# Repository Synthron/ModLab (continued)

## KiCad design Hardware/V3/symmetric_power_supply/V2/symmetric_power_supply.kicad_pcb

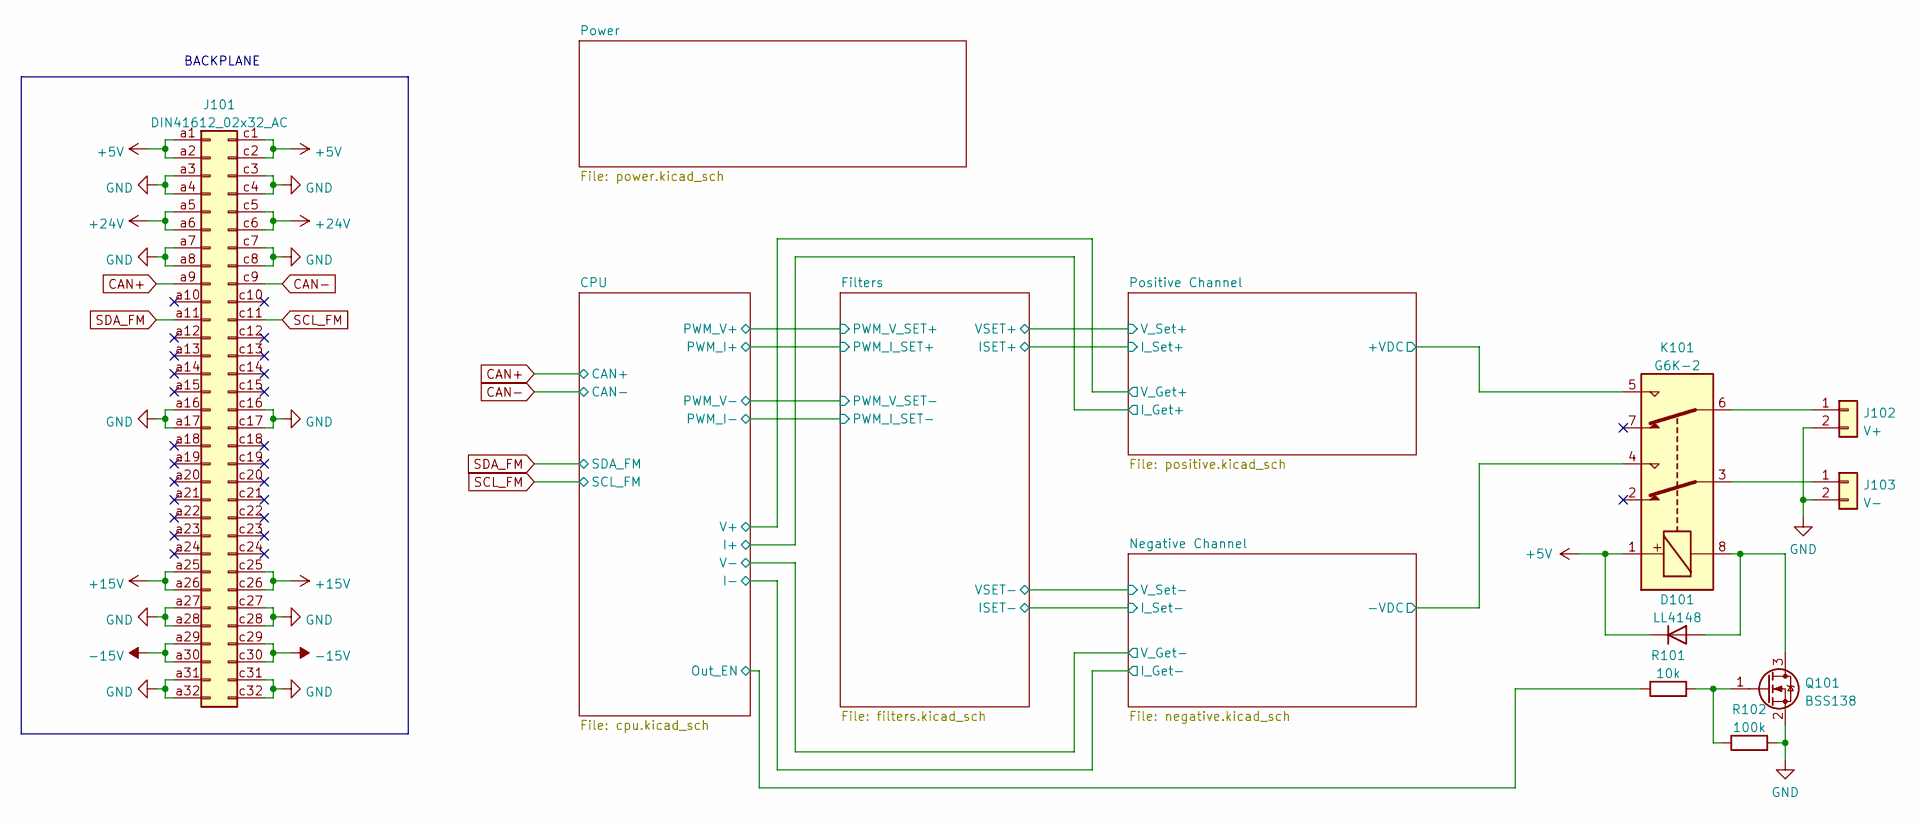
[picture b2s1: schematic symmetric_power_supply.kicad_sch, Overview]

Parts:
D101: LL4148; D_MiniMELF
J101: DIN41612_02x32_AC; VG64_Euro
J102: V+; PinHeader_1x02_P2.54mm_Vertical
J103: V-; PinHeader_1x02_P2.54mm_Vertical
K101: G6K-2; Relay_DPDT_Omron_G6K-2F
Q101: BSS138; SOT-23
R101: 10k; R_0805_2012Metric
R102: 100k; R_0805_2012Metric

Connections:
+5V: D101.1 (K), J101.a1, J101.a2, J101.c1, J101.c2, K101.1; also elsewhere on the board
+15V: J101.a25, J101.a26, J101.c25, J101.c26; also elsewhere on the board
+24V: J101.a5, J101.a6, J101.c5, J101.c6; also elsewhere on the board
+VDC: K101.5; also elsewhere on the board
-15V: J101.a29, J101.a30, J101.c29, J101.c30; also elsewhere on the board
-VDC: K101.4; also elsewhere on the board
/CPU/Out_EN: R101.1; also elsewhere on the board
CAN+: J101.a9; also elsewhere on the board
CAN-: J101.c9; also elsewhere on the board
GND: J101.a3, J101.a4, J101.a7, J101.a8, J101.a16, J101.a17, J101.a27, J101.a28, J101.a31, J101.a32, J101.c3, J101.c4, J101.c7, J101.c8, J101.c16, J101.c17, J101.c27, J101.c28, J101.c31, J101.c32, J102.2, J103.2, Q101.2 (S), R102.2; also elsewhere on the board
unnamed: D101.2 (A), K101.8, Q101.3 (D)
unnamed: J102.1, K101.6
unnamed: J103.1, K101.3
unnamed: Q101.1 (G), R101.2, R102.1
SCL_FM: J101.c11; also elsewhere on the board
SDA_FM: J101.a11; also elsewhere on the board

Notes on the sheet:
BACKPLANE

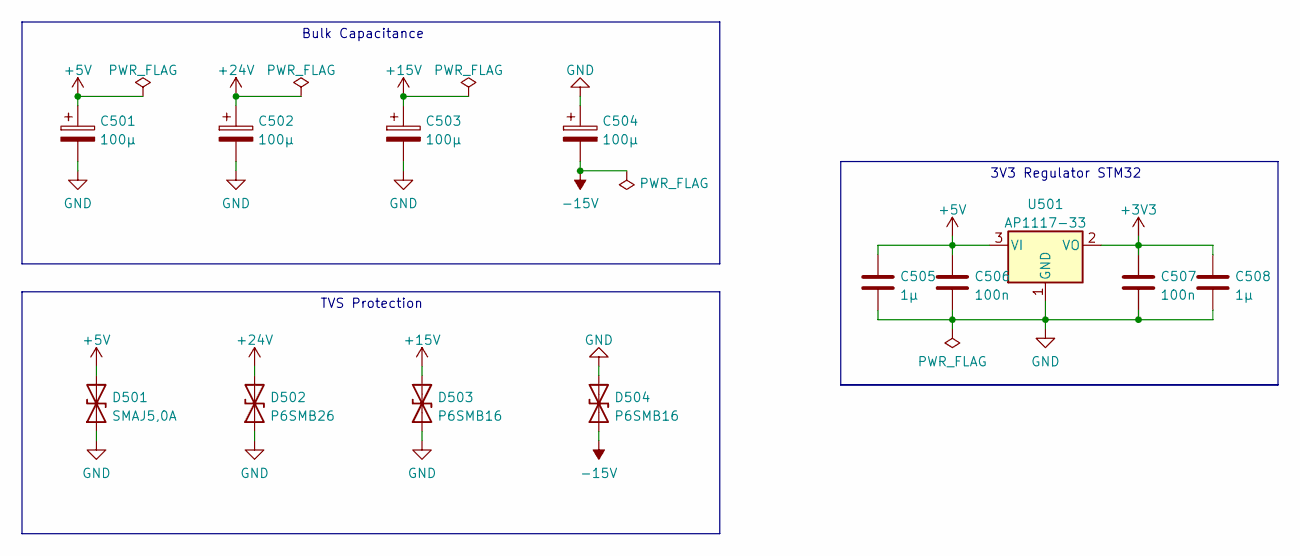
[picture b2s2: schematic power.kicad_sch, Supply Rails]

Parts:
C501, C502, C503, C504: 100µ; CP_Radial_D8.0mm_P5.00mm
C505, C508: 1µ; C_0805_2012Metric
C506, C507: 100n; C_0805_2012Metric
D501: SMAJ5,0A; D_SMA
D502: P6SMB26; D_SMA
D503, D504: P6SMB16; D_SMA
U501: AP1117-33; SOT-223-3_TabPin2

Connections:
+3V3: C507.1, C508.1, U501.2 (VO); also elsewhere on the board
+5V: C501.1, C505.1, C506.1, D501.2 (A2), U501.3 (VI); also elsewhere on the board
+15V: C503.1, D503.2 (A2); also elsewhere on the board
+24V: C502.1, D502.2 (A2); also elsewhere on the board
-15V: C504.2, D504.1 (A1); also elsewhere on the board
GND: C501.2, C502.2, C503.2, C504.1, C505.2, C506.2, C507.2, C508.2, D501.1 (A1), D502.1 (A1), D503.1 (A1), D504.2 (A2), U501.1 (GND); also elsewhere on the board

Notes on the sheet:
Bulk Capacitance
TVS Protection
3V3 Regulator STM32

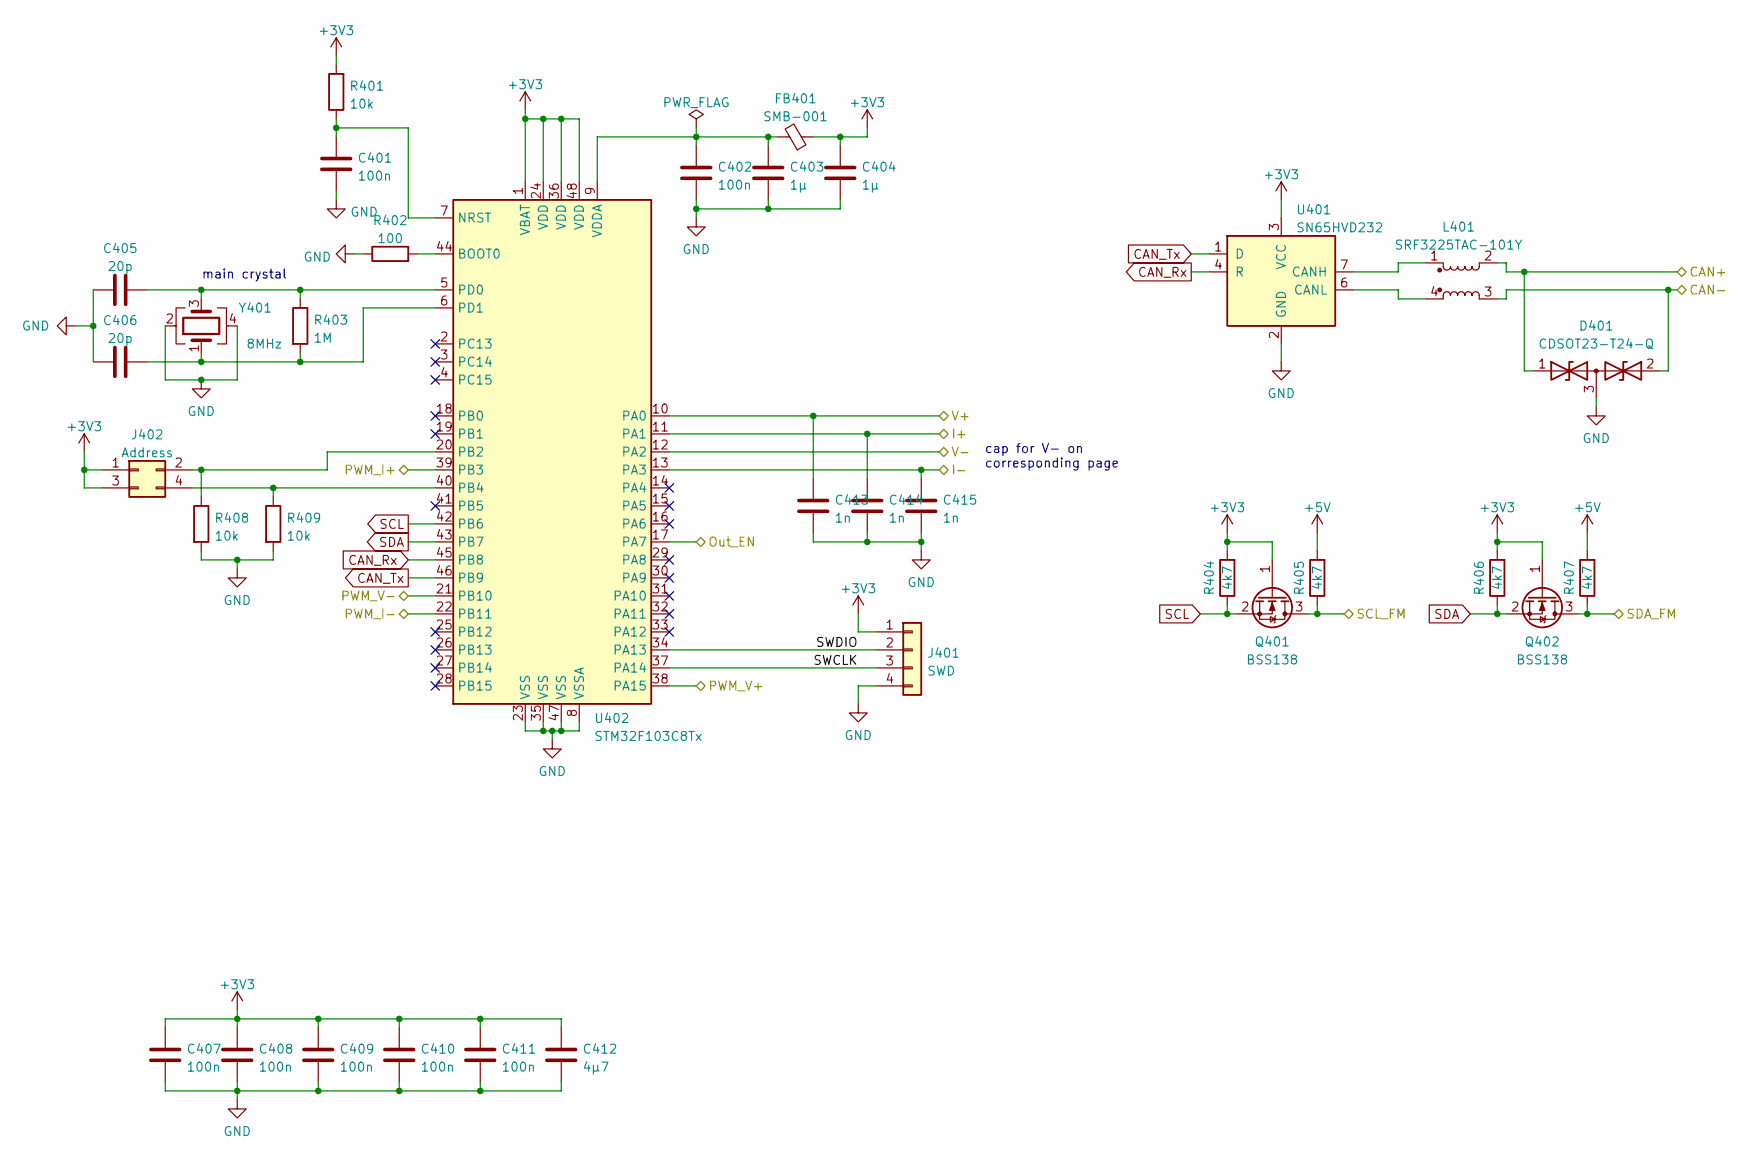
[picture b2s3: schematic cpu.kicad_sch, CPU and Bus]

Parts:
C401, C402, C407, C408, C409, C410, C411: 100n; C_0805_2012Metric
C403, C404: 1µ; C_0805_2012Metric
C405, C406: 20p; C_0805_2012Metric
C412: 4µ7; C_0805_2012Metric
C413, C414, C415: 1n; C_0805_2012Metric
D401: CDSOT23-T24-Q; SOT-23
FB401: SMB-001
J401: SWD; JST_XH_B4B-XH-A_1x04_P2.50mm_Vertical
J402: Address; PinHeader_2x02_P2.54mm_Vertical
L401: SRF3225TAC-101Y; SRF3225TAC
Q401, Q402: BSS138; SOT-23
R401, R408, R409: 10k; R_0805_2012Metric
R402: 100; R_0805_2012Metric
R403: 1M; R_0805_2012Metric
R404, R405, R406, R407: 4k7; R_0805_2012Metric
U401: SN65HVD232; SOIC-8_3.9x4.9mm_P1.27mm
U402: STM32F103C8Tx; LQFP-48_7x7mm_P0.5mm
Y401: 8MHz; Crystal_SMD_5032-4Pin_5.0x3.2mm

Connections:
+3V3: C404.1, C407.1, C408.1, C409.1, C410.1, C411.1, C412.1, FB401.1, J401.1, J402.1, J402.3, Q401.1 (G), Q402.1 (G), R401.2, R404.2, R406.2, U401.3 (VCC), U402.1 (VBAT), U402.24 (VDD), U402.36 (VDD), U402.48 (VDD); also elsewhere on the board
+5V: R405.2, R407.2; also elsewhere on the board
/CPU/I+: C414.1, U402.11 (PA1); also elsewhere on the board
/CPU/I-: C415.1, U402.13 (PA3); also elsewhere on the board
/CPU/Out_EN: U402.17 (PA7); also elsewhere on the board
/CPU/PWM_I+: U402.39 (PB3); also elsewhere on the board
/CPU/PWM_I-: U402.22 (PB11); also elsewhere on the board
/CPU/PWM_V+: U402.38 (PA15); also elsewhere on the board
/CPU/PWM_V-: U402.21 (PB10); also elsewhere on the board
/CPU/SWCLK: J401.3, U402.37 (PA14)
/CPU/SWDIO: J401.2, U402.34 (PA13)
/CPU/V+: C413.1, U402.10 (PA0); also elsewhere on the board
/CPU/V-: U402.12 (PA2); also elsewhere on the board
CAN+: D401.1 (A1), L401.2; also elsewhere on the board
CAN-: D401.2 (A2), L401.3; also elsewhere on the board
CAN_Rx: U401.4 (R), U402.45 (PB8)
CAN_Tx: U401.1 (D), U402.46 (PB9)
GND: C401.2, C402.2, C403.2, C404.2, C405.1, C406.1, C407.2, C408.2, C409.2, C410.2, C411.2, C412.2, C413.2, C414.2, C415.2, D401.3 (common), J401.4, R402.1, R408.2, R409.2, U401.2 (GND), U402.8 (VSSA), U402.23 (VSS), U402.35 (VSS), U402.47 (VSS), Y401.2, Y401.4; also elsewhere on the board
unnamed: C401.1, R401.1, U402.7 (NRST)
unnamed: C402.1, C403.1, FB401.2, U402.9 (VDDA)
unnamed: C405.2, R403.1, U402.5 (PD0), Y401.3
unnamed: C406.2, R403.2, U402.6 (PD1), Y401.1
unnamed: J402.2, R408.1, U402.20 (PB2)
unnamed: J402.4, R409.1, U402.40 (PB4)
unnamed: L401.1, U401.7 (CANH)
unnamed: L401.4, U401.6 (CANL)
unnamed: R402.2, U402.44 (BOOT0)
SCL: Q401.2 (S), R404.1, U402.42 (PB6)
SCL_FM: Q401.3 (D), R405.1; also elsewhere on the board
SDA: Q402.2 (S), R406.1, U402.43 (PB7)
SDA_FM: Q402.3 (D), R407.1; also elsewhere on the board

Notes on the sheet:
main crystal
cap for V- on corresponding page

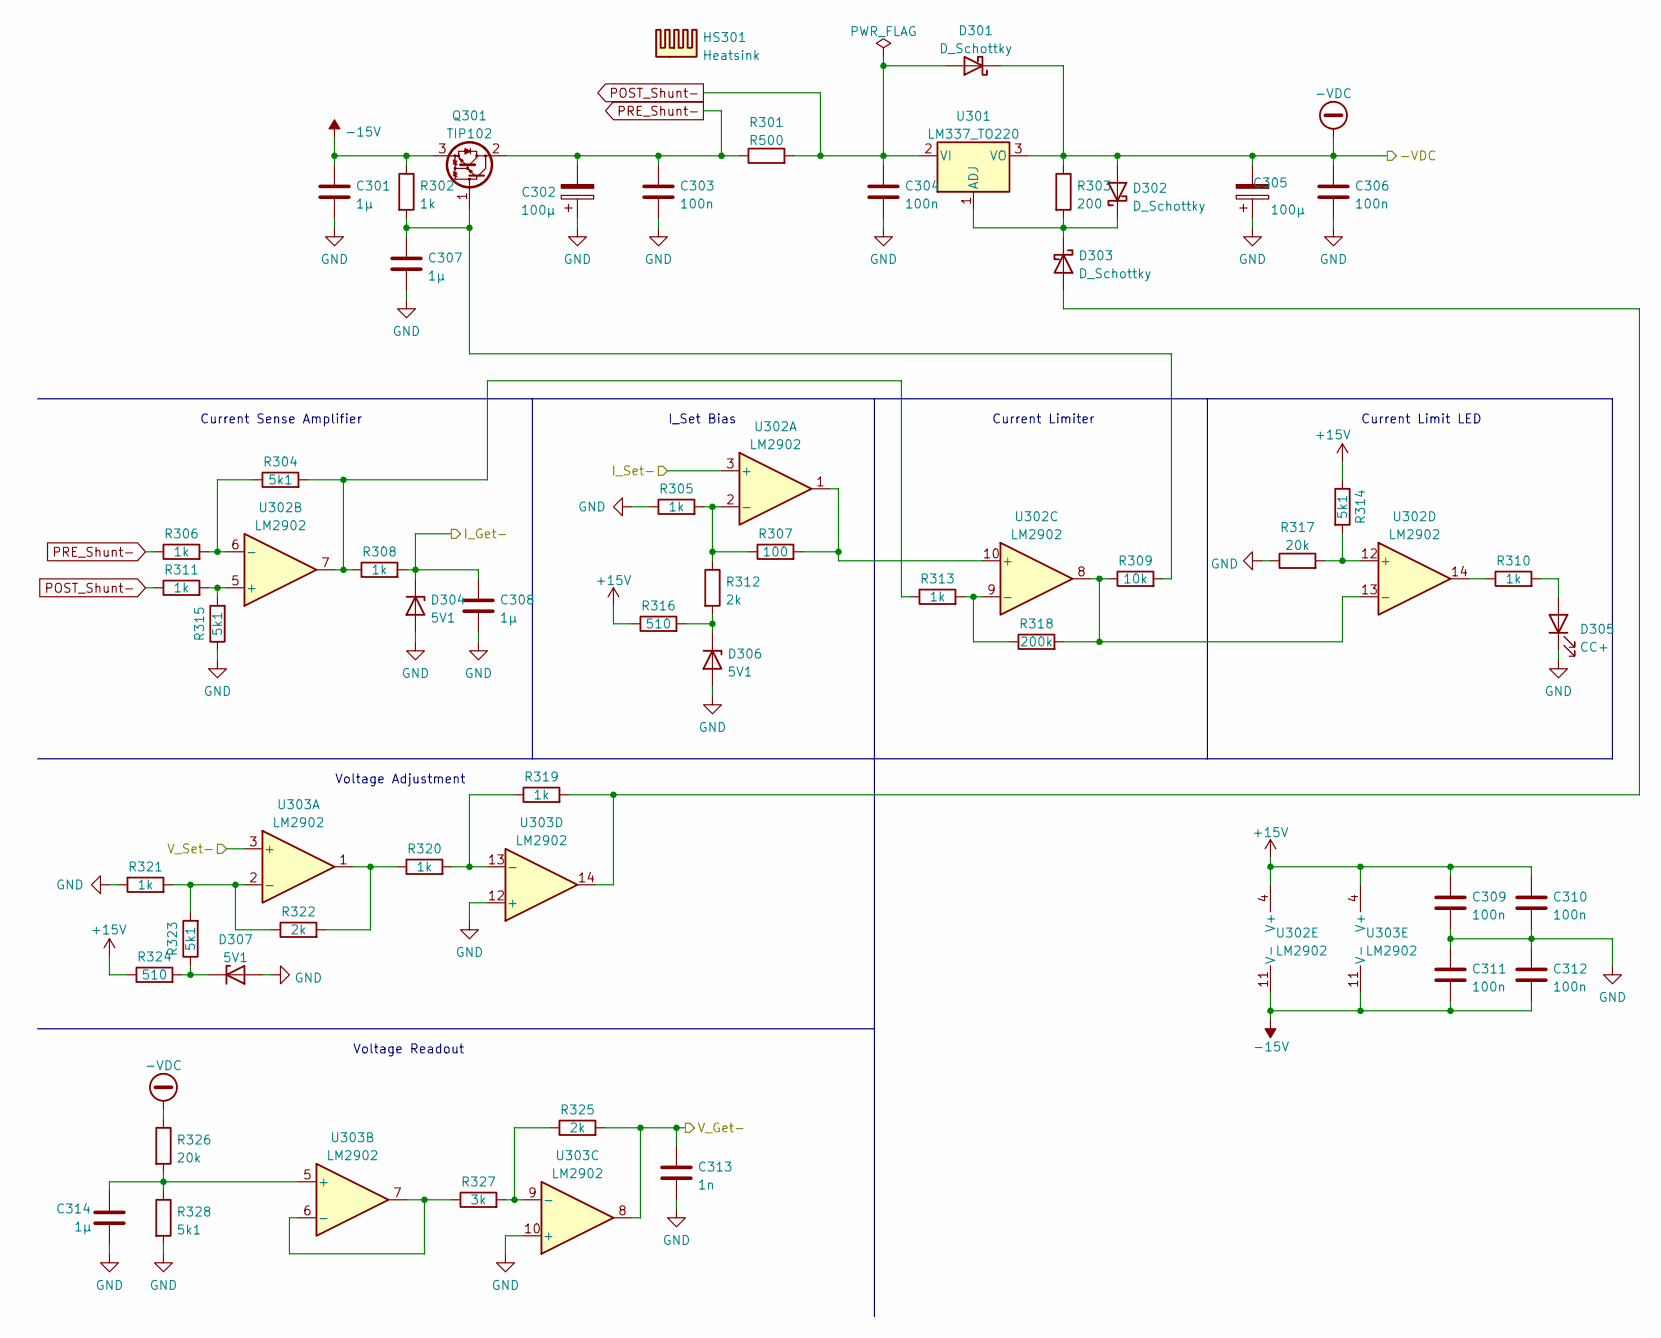
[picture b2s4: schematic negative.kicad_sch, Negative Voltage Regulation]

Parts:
C301, C307, C308, C314: 1µ; C_0805_2012Metric
C302, C305: 100µ; CP_Elec_5x5.8
C303, C304, C306, C309, C310, C311, C312: 100n; C_0805_2012Metric
C313: 1n; C_0805_2012Metric
D301, D302, D303: D_Schottky; D_SOD-123
D304, D306, D307: 5V1; D_SOD-123
D305: CC+; LED_D3.0mm
HS301: Heatsink; SK574-50
Q301: TIP102; TO-220-3_Vertical
R301: R500; R_2512_6332Metric
R302, R305, R306, R308, R310, R311, R313, R319, R320, R321: 1k; R_0805_2012Metric
R303: 200; R_0805_2012Metric
R304, R314, R315, R323, R328: 5k1; R_0805_2012Metric
R307: 100; R_0805_2012Metric
R309: 10k; R_0805_2012Metric
R312, R322, R325: 2k; R_0805_2012Metric
R316, R324: 510; R_0805_2012Metric
R317, R326: 20k; R_0805_2012Metric
R318: 200k; R_0805_2012Metric
R327: 3k; R_0805_2012Metric
U301: LM337_TO220; TO-220-3_Vertical
U302, U303: LM2902; TSSOP-14_4.4x5mm_P0.65mm

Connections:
+15V: C309.1, C310.1, R314.1, R316.1, R324.1, U302.4 (V+), U303.4 (V+); also elsewhere on the board
-15V: C301.1, C311.2, C312.2, Q301.3 (E), R302.1, U302.11 (V-), U303.11 (V-); also elsewhere on the board
-VDC: C305.2, C306.1, D301.1 (K), D302.2 (A), R303.1, R326.1, U301.3 (VO); also elsewhere on the board
/CPU/I-: C308.1, D304.1 (K), R308.2; also elsewhere on the board
/CPU/V-: C313.1, R325.2, U303.8; also elsewhere on the board
/Filters/ISET-: U302.3 (+); also elsewhere on the board
/Filters/VSET-: U303.3 (+); also elsewhere on the board
GND: C301.2, C302.1, C303.2, C304.2, C305.1, C306.2, C307.2, C308.2, C309.2, C310.2, C311.1, C312.1, C313.2, C314.2, D304.2 (A), D305.1 (K), D306.2 (A), D307.2 (A), R305.1, R315.1, R317.1, R321.1, R328.2, U303.10 (+), U303.12 (+); also elsewhere on the board
unnamed: C307.1, Q301.1 (B), R302.2, R309.2
unnamed: C314.1, R326.2, R328.1, U303.5 (+)
unnamed: D302.1 (K), D303.1 (K), R303.2, U301.1 (ADJ)
unnamed: D303.2 (A), R319.2, U303.14
unnamed: D305.2 (A), R310.2
unnamed: D306.1 (K), R312.2, R316.2
unnamed: D307.1 (K), R323.1, R324.2
unnamed: R304.1, R306.2, U302.6 (-)
unnamed: R304.2, R308.1, R313.1, U302.7
unnamed: R305.2, R307.1, R312.1, U302.2 (-)
unnamed: R307.2, U302.1, U302.10 (+)
unnamed: R309.1, R318.2, U302.8, U302.13 (-)
unnamed: R310.1, U302.14
unnamed: R311.2, R315.2, U302.5 (+)
unnamed: R313.2, R318.1, U302.9 (-)
unnamed: R319.1, R320.2, U303.13 (-)
unnamed: R320.1, R322.2, U303.1
unnamed: R321.2, R322.1, R323.2, U303.2 (-)
unnamed: R325.1, R327.2, U303.9 (-)
unnamed: R327.1, U303.6 (-), U303.7
unnamed: R314.2, R317.2, U302.12 (+)
POST_Shunt-: C304.1, D301.2 (A), R301.2, R311.1, U301.2 (VI)
PRE_Shunt-: C302.2, C303.1, Q301.2 (C), R301.1, R306.1

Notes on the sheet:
Current Sense Amplifier
I_Set Bias
Voltage Adjustment
Current Limit LED
Voltage Readout
Current Limiter

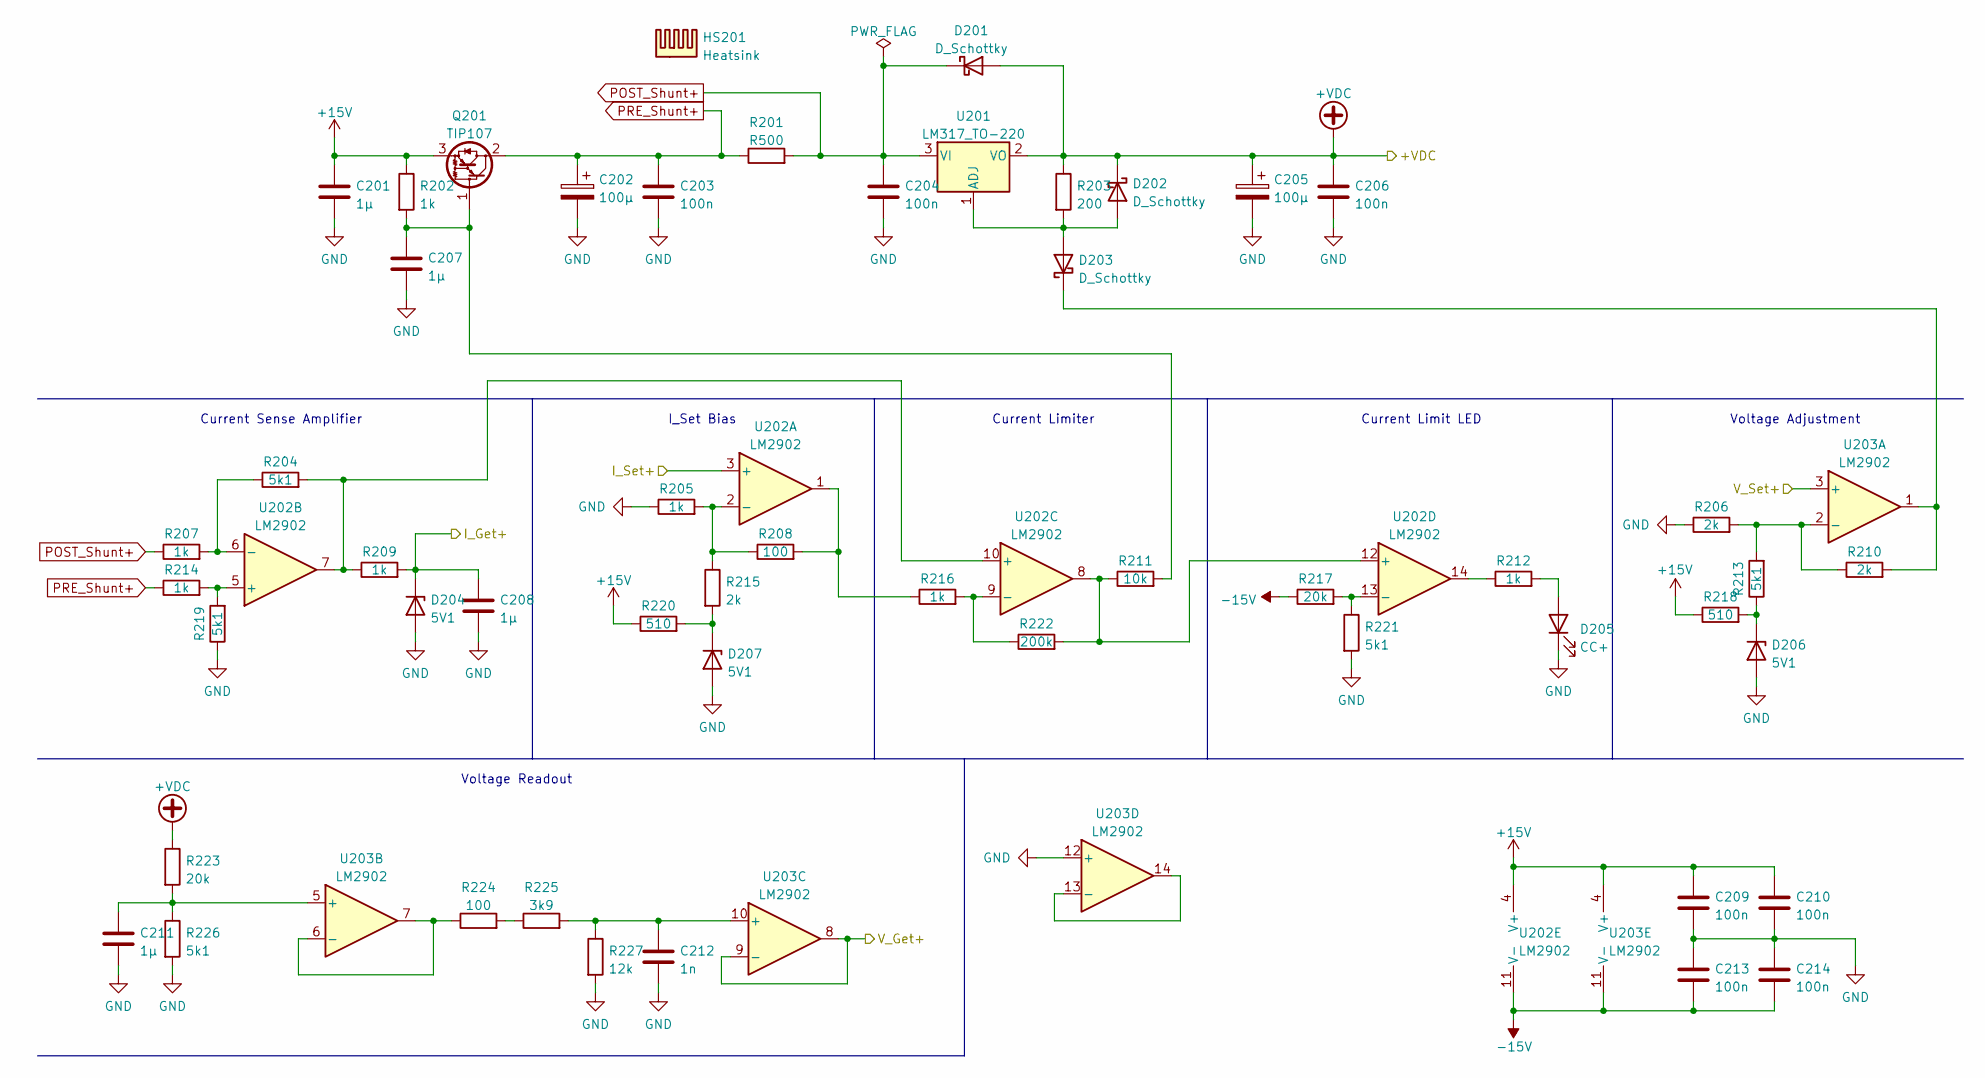
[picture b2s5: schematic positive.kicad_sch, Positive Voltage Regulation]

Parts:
C201, C207, C208, C211: 1µ; C_0805_2012Metric
C202, C205: 100µ; CP_Elec_5x5.8
C203, C204, C206, C209, C210, C213, C214: 100n; C_0805_2012Metric
C212: 1n; C_0805_2012Metric
D201, D202, D203: D_Schottky; D_SOD-123
D204, D206, D207: 5V1; D_SOD-123
D205: CC+; LED_D3.0mm
HS201: Heatsink; SK574-50
Q201: TIP107; TO-220-3_Vertical
R201: R500; R_2512_6332Metric
R202, R205, R207, R209, R212, R214, R216: 1k; R_0805_2012Metric
R203: 200; R_0805_2012Metric
R204, R213, R219, R221, R226: 5k1; R_0805_2012Metric
R206, R210, R215: 2k; R_0805_2012Metric
R208, R224: 100; R_0805_2012Metric
R211: 10k; R_0805_2012Metric
R217, R223: 20k; R_0805_2012Metric
R218, R220: 510; R_0805_2012Metric
R222: 200k; R_0805_2012Metric
R225: 3k9; R_0805_2012Metric
R227: 12k; R_0805_2012Metric
U201: LM317_TO-220; TO-220-3_Vertical
U202, U203: LM2902; TSSOP-14_4.4x5mm_P0.65mm

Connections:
+15V: C201.1, C209.1, C210.1, Q201.3 (E), R202.1, R218.1, R220.1, U202.4 (V+), U203.4 (V+); also elsewhere on the board
+VDC: C205.1, C206.1, D201.2 (A), D202.1 (K), R203.1, R223.1, U201.2 (VO); also elsewhere on the board
-15V: C213.2, C214.2, R217.1, U202.11 (V-), U203.11 (V-); also elsewhere on the board
/CPU/I+: C208.1, D204.1 (K), R209.2; also elsewhere on the board
/CPU/V+: U203.8, U203.9 (-); also elsewhere on the board
/Filters/ISET+: U202.3 (+); also elsewhere on the board
/Filters/VSET+: U203.3 (+); also elsewhere on the board
GND: C201.2, C202.2, C203.2, C204.2, C205.2, C206.2, C207.2, C208.2, C209.2, C210.2, C211.2, C212.2, C213.1, C214.1, D204.2 (A), D205.1 (K), D206.2 (A), D207.2 (A), R205.1, R206.1, R219.1, R221.2, R226.2, R227.2, U203.12 (+); also elsewhere on the board
unnamed: C207.1, Q201.1 (B), R202.2, R211.2
unnamed: C211.1, R223.2, R226.1, U203.5 (+)
unnamed: C212.1, R225.2, R227.1, U203.10 (+)
unnamed: D202.2 (A), D203.2 (A), R203.2, U201.1 (ADJ)
unnamed: D203.1 (K), R210.2, U203.1
unnamed: D205.2 (A), R212.2
unnamed: D206.1 (K), R213.1, R218.2
unnamed: D207.1 (K), R215.2, R220.2
unnamed: R204.1, R207.2, U202.6 (-)
unnamed: R204.2, R209.1, U202.7, U202.10 (+)
unnamed: R205.2, R208.1, R215.1, U202.2 (-)
unnamed: R206.2, R210.1, R213.2, U203.2 (-)
unnamed: R208.2, R216.1, U202.1
unnamed: R211.1, R222.2, U202.8, U202.12 (+)
unnamed: R212.1, U202.14
unnamed: R214.2, R219.2, U202.5 (+)
unnamed: R216.2, R222.1, U202.9 (-)
unnamed: R217.2, R221.1, U202.13 (-)
unnamed: R224.1, U203.6 (-), U203.7
unnamed: R224.2, R225.1
unnamed: U203.13 (-), U203.14
POST_Shunt+: C204.1, D201.1 (K), R201.2, R207.1, U201.3 (VI)
PRE_Shunt+: C202.1, C203.1, Q201.2 (C), R201.1, R214.1

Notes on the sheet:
I_Set Bias
Voltage Readout
Current Sense Amplifier
Current Limit LED
Current Limiter
Voltage Adjustment

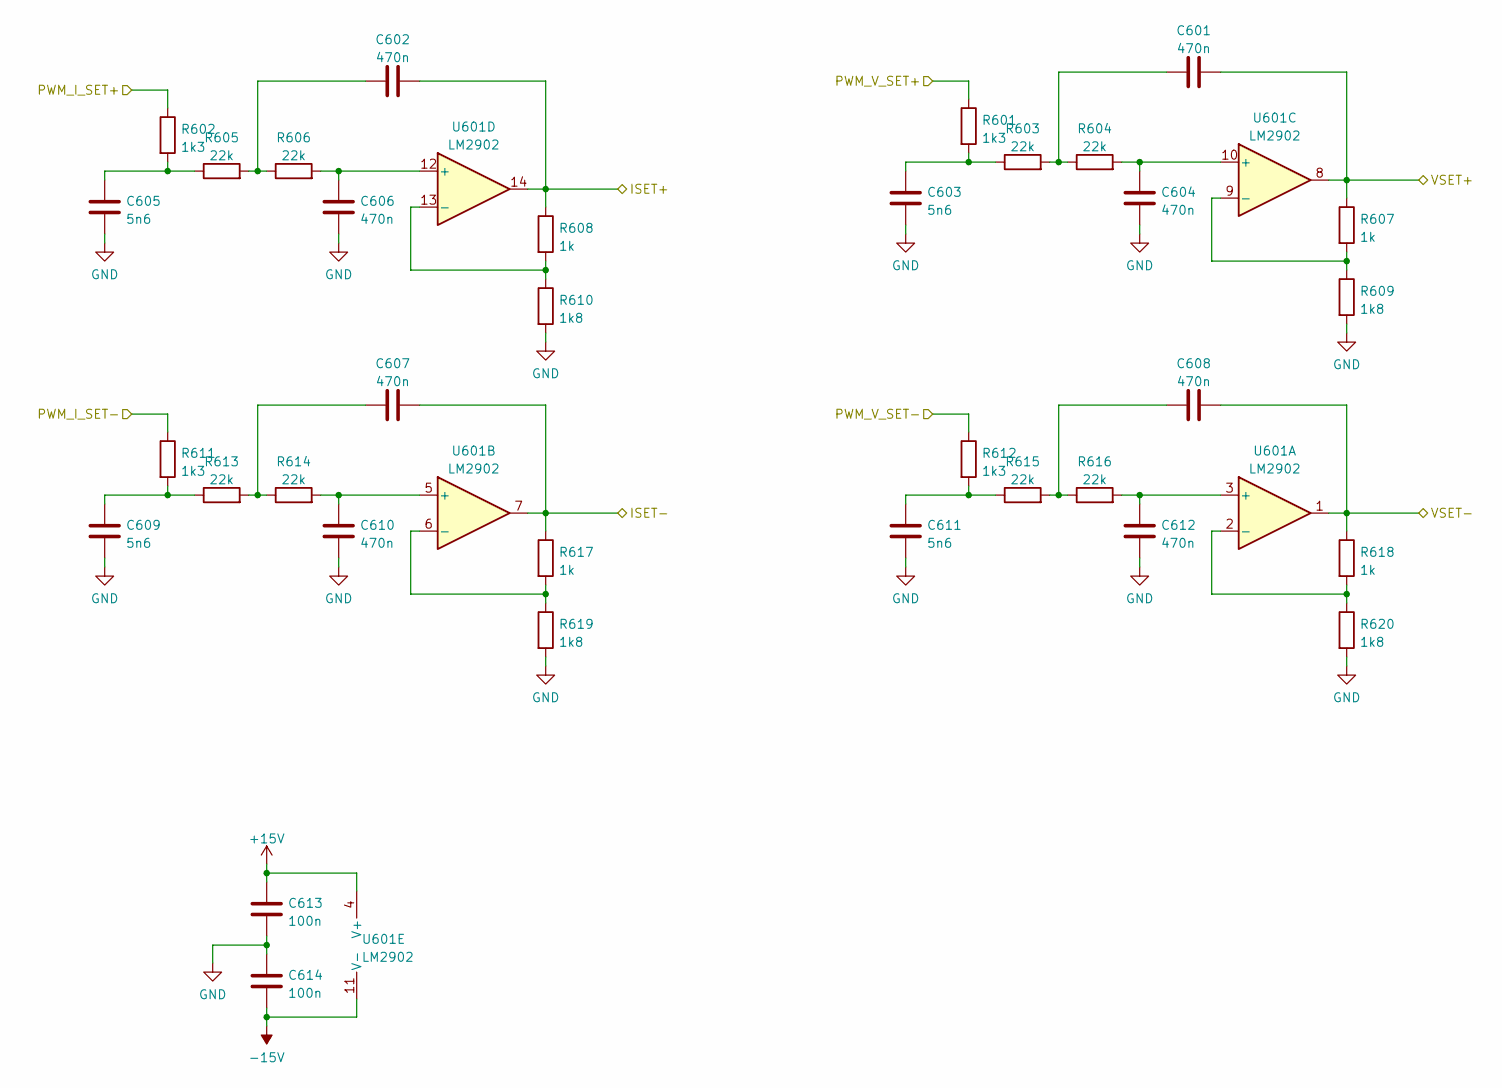
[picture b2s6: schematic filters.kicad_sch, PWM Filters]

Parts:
C601, C602, C604, C606, C607, C608, C610, C612: 470n; C_0805_2012Metric
C603, C605, C609, C611: 5n6; C_0805_2012Metric
C613, C614: 100n; C_0805_2012Metric
R601, R602, R611, R612: 1k3; R_0805_2012Metric
R603, R604, R605, R606, R613, R614, R615, R616: 22k; R_0805_2012Metric
R607, R608, R617, R618: 1k; R_0805_2012Metric
R609, R610, R619, R620: 1k8; R_0805_2012Metric
U601: LM2902; TSSOP-14_4.4x5mm_P0.65mm

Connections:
+15V: C613.1, U601.4 (V+); also elsewhere on the board
-15V: C614.2, U601.11 (V-); also elsewhere on the board
/CPU/PWM_I+: R602.1; also elsewhere on the board
/CPU/PWM_I-: R611.1; also elsewhere on the board
/CPU/PWM_V+: R601.1; also elsewhere on the board
/CPU/PWM_V-: R612.1; also elsewhere on the board
/Filters/ISET+: C602.2, R608.1, U601.14; also elsewhere on the board
/Filters/ISET-: C607.2, R617.1, U601.7; also elsewhere on the board
/Filters/VSET+: C601.2, R607.1, U601.8; also elsewhere on the board
/Filters/VSET-: C608.2, R618.1, U601.1; also elsewhere on the board
GND: C603.2, C604.2, C605.2, C606.2, C609.2, C610.2, C611.2, C612.2, C613.2, C614.1, R609.2, R610.2, R619.2, R620.2; also elsewhere on the board
unnamed: C601.1, R603.2, R604.1
unnamed: C602.1, R605.2, R606.1
unnamed: C603.1, R601.2, R603.1
unnamed: C604.1, R604.2, U601.10 (+)
unnamed: C605.1, R602.2, R605.1
unnamed: C606.1, R606.2, U601.12 (+)
unnamed: C607.1, R613.2, R614.1
unnamed: C608.1, R615.2, R616.1
unnamed: C609.1, R611.2, R613.1
unnamed: C610.1, R614.2, U601.5 (+)
unnamed: C611.1, R612.2, R615.1
unnamed: C612.1, R616.2, U601.3 (+)
unnamed: R607.2, R609.1, U601.9 (-)
unnamed: R608.2, R610.1, U601.13 (-)
unnamed: R617.2, R619.1, U601.6 (-)
unnamed: R618.2, R620.1, U601.2 (-)

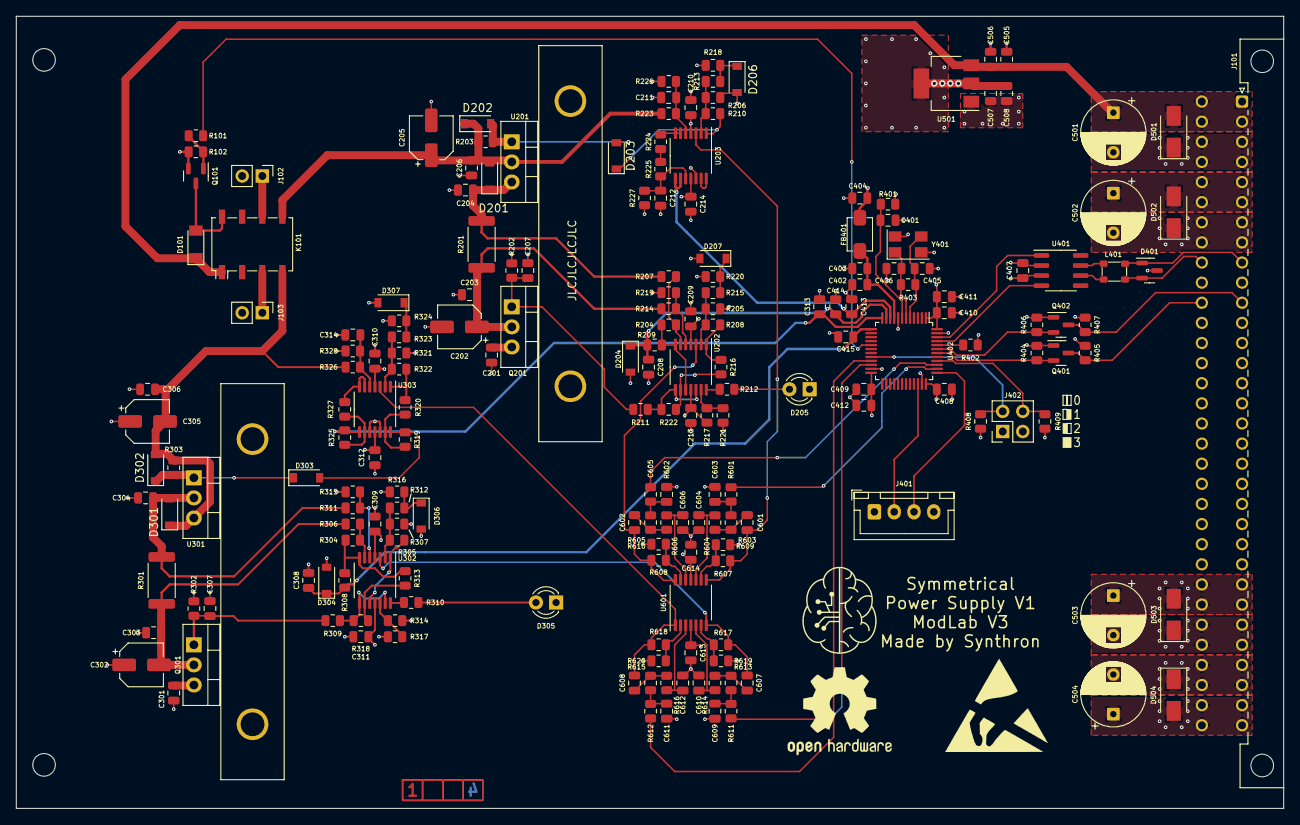
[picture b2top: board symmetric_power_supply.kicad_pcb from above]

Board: 4 copper layers, 160.0 x 100.0 mm, 197 parts (0 on the bottom side), 106 nets.

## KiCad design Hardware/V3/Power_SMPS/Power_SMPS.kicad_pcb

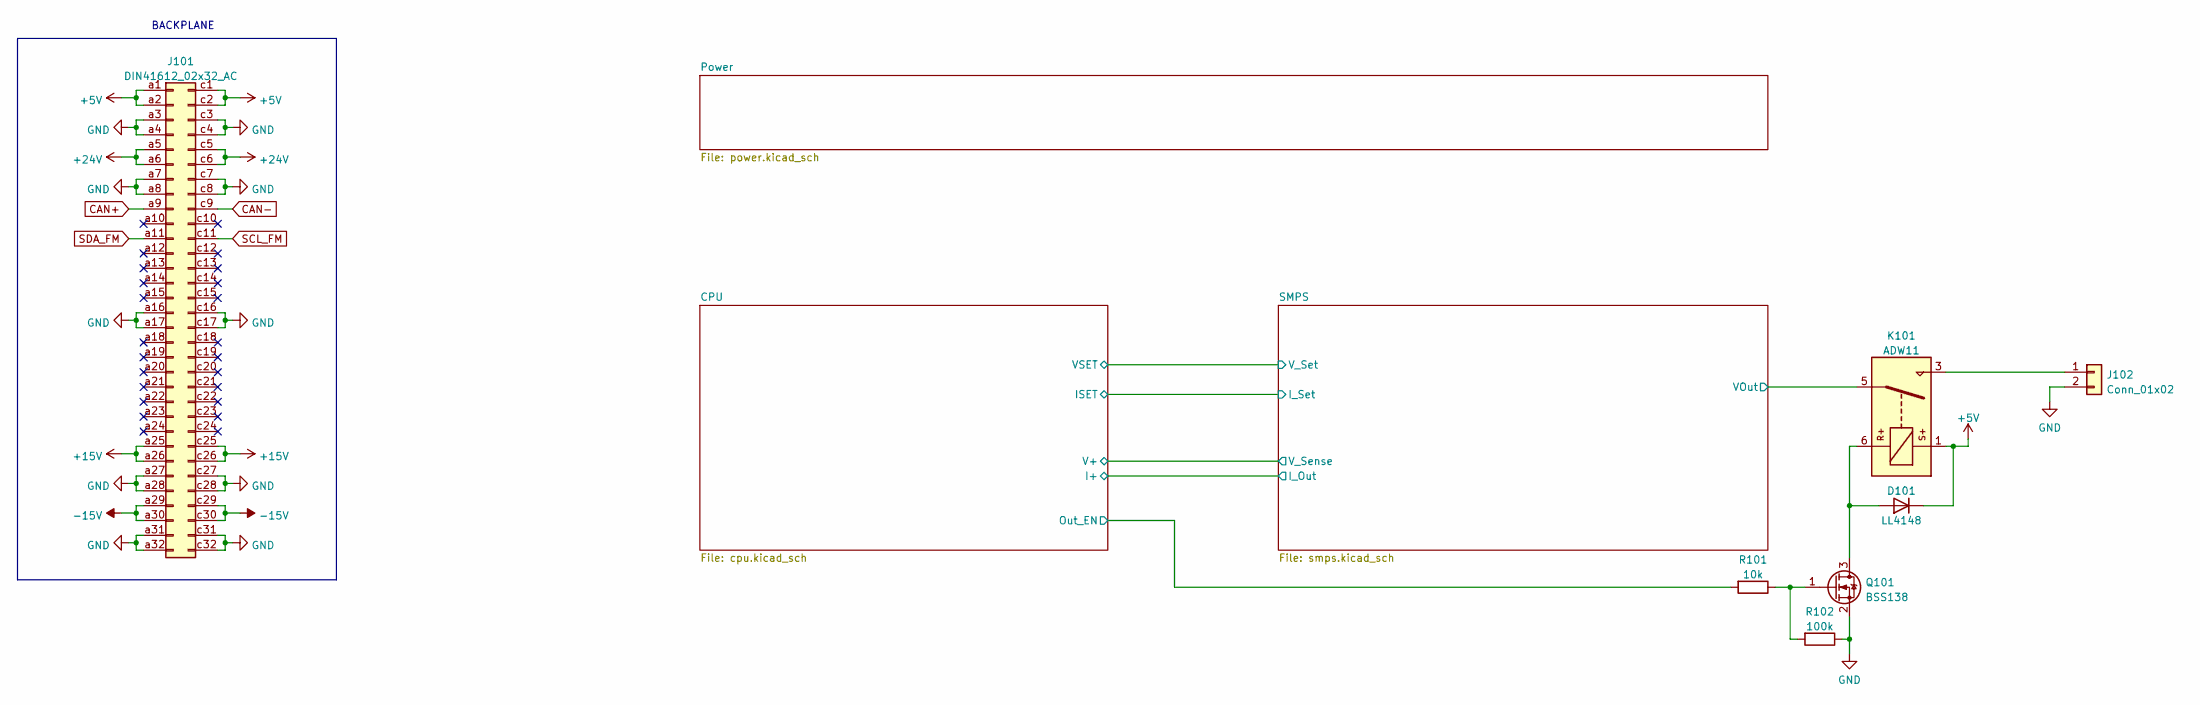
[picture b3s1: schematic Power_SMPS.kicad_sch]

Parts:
D101: LL4148; D_MiniMELF
J101: DIN41612_02x32_AC; VG64_Euro
J102: Conn_01x02; PinSocket_1x02_P2.54mm_Vertical
K101: ADW11; JS 05 MN KT
Q101: BSS138; SOT-23
R101: 10k; R_0805_2012Metric
R102: 100k; R_0805_2012Metric

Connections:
+5V: D101.1 (K), J101.a1, J101.a2, J101.c1, J101.c2, K101.1; also elsewhere on the board
+15V: J101.a25, J101.a26, J101.c25, J101.c26; also elsewhere on the board
+24V: J101.a5, J101.a6, J101.c5, J101.c6; also elsewhere on the board
-15V: J101.a29, J101.a30, J101.c29, J101.c30; also elsewhere on the board
/CPU/Out_EN: R101.2; also elsewhere on the board
/SMPS/VOut: K101.5; also elsewhere on the board
CAN+: J101.a9; also elsewhere on the board
CAN-: J101.c9; also elsewhere on the board
GND: J101.a3, J101.a4, J101.a7, J101.a8, J101.a16, J101.a17, J101.a27, J101.a28, J101.a31, J101.a32, J101.c3, J101.c4, J101.c7, J101.c8, J101.c16, J101.c17, J101.c27, J101.c28, J101.c31, J101.c32, J102.2, Q101.2 (S), R102.1; also elsewhere on the board
unnamed: D101.2 (A), K101.6, Q101.3 (D)
unnamed: J102.1, K101.3
unnamed: Q101.1 (G), R101.1, R102.2
SCL_FM: J101.c11; also elsewhere on the board
SDA_FM: J101.a11; also elsewhere on the board

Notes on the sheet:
BACKPLANE
